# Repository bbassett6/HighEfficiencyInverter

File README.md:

Project Executive Summary

What is the design problem and why it should be solved?

With the growing popularity of student-led solar car racing competitions, newly established teams can have restrictive levels of funding to start their engineering endeavors. One of the most critical components of the competitiveness of their cars is the powertrain efficiency, which is heavily influenced by the quality and versatility of their motor controller. As of today, there are only two competitive options that are adopted by most teams, and both represent a substantial amount of the vehicle's cost (over a third of the electrical system's, approximately). This creates a tall barrier of entry for developing engineers to be exposed to real-life design environments that could deeply affect their career choices and subsequent impact in the world, which is why an open-source, accessible inverter would be impactful in the field of sustainable energy, and potentially many others.

What are the technical problems?

Technical problems include
•	Obtaining efficiency range values comparable or superior to present competitors’ while offering a substantially reduced price: 
Because of the size of the market, no substantial innovation has been made in mainstream options for approximately 14 years. Recent developments in SiC and GaN-based semiconductors could contribute a significant advantage compared to these outdated designs, but hitting required performance levels for a large range of possible motor and voltage configurations will be a challenge. Additionally, new control methodologies might be more applicable nowadays because of both device development and advances in control theory.
•	Maximizing efficiency while keeping the inverter design as tolerant as possible to high-voltage design changes depending on the application: 
Teams' choices of power per motor and DC bus voltage can vary drastically depending on the competition segment (multi- or single-occupant vehicles), creating a challenging optimization problem when attempting to make a product as efficient as possible for as many configurations as expected.
•	Minimizing inverter-driven high voltage system requirements: 
In addition to the DC bus compatibility, motor and motor sensing versatility is a factor that influences how seamless the product's integration can be, facilitating its adoption and potentially expanding its impact.
•	Power density (gravimetric, volumetric):
Being heavily influenced by the switching speed of the semiconductor devices being employed, recent product releases could be incredibly important to meet performance levels such as the DOE's 2025 Vehicle Technology goals.

What is the overall design/technical/objective(s)?

Design a financially (under US$ 1000) and technically accessible, high efficiency inverter for use in solar vehicle applications. The design should be easily replicable, testable, and employed by high-school level students. The final efficiency characteristics for applicable performance ranges (e.g. torque, speed, temperature), should be compatible with or surpass those of available options (WaveSculptor22, Mitsuba).

What is the proof of concept? What demonstrates that the solution works?

The proof of concept for the project could consist of a custom-made PCB for the selected power stage topology, containing components such as the switching devices, gate drivers, & high-voltage sensors. This would be complemented with an off-the-shelf development board containing the selected microcontroller and required peripherals, allowing full validation and operation of the converter without a finalized case and custom logic-stage PCB. Should this implementation work as expected, the project would move forward to unification and/or further customization of the boards to achieve a final unified package that is easily integrable.

Demonstrating the solution may involve attaching either an inductive load or a real motor to the inverter and measuring power losses through the power stage at various operating points (steady state cruising, acceleration, regenerative braking).

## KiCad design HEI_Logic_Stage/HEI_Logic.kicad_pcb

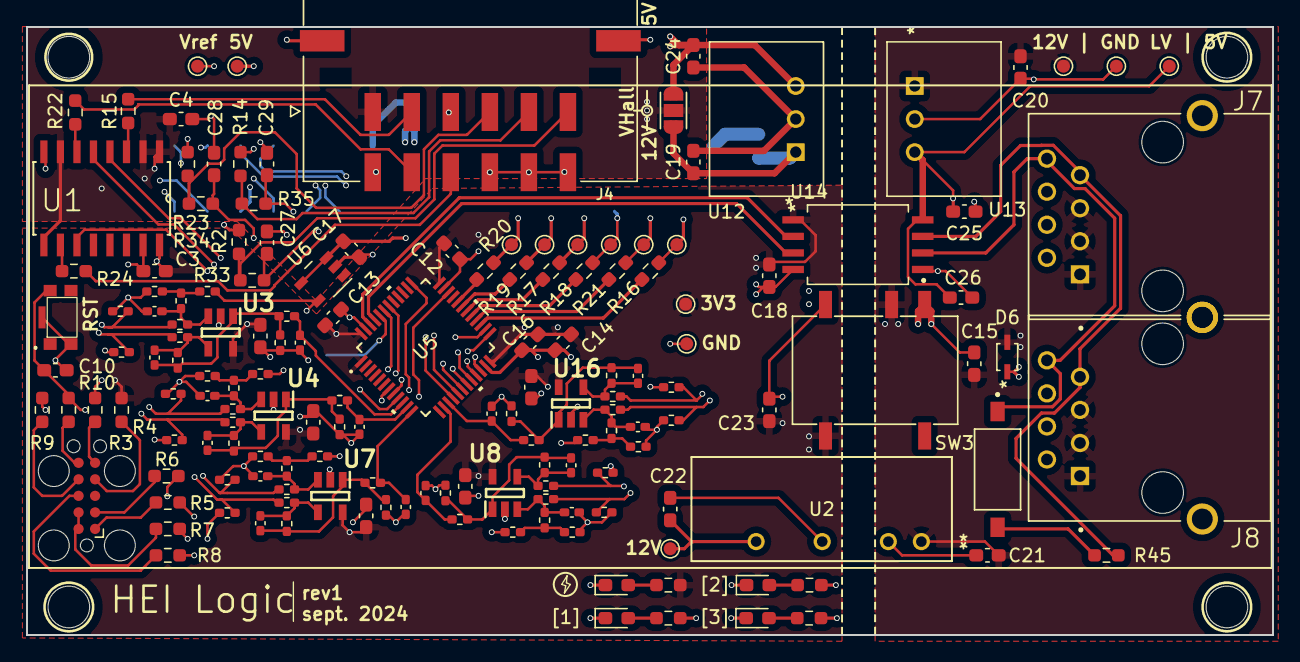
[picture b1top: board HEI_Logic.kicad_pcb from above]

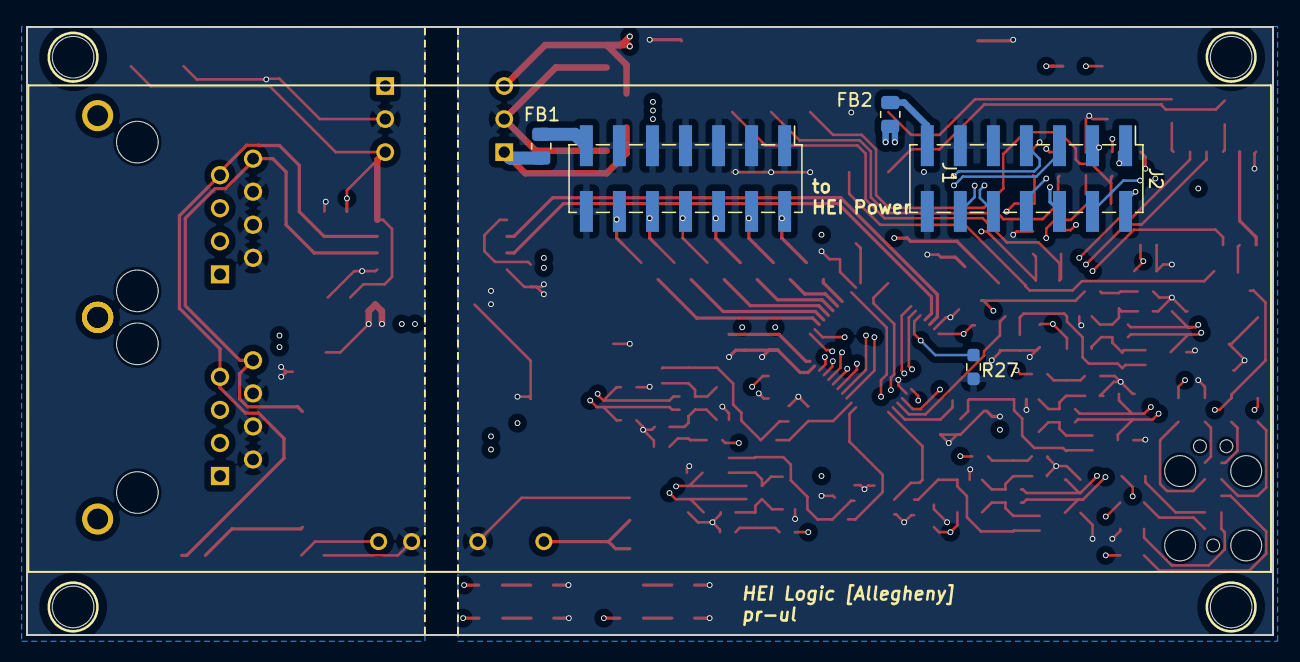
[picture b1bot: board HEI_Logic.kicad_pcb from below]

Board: 4 copper layers, 95.8 x 46.7 mm, 167 parts (5 on the bottom side), 99 nets.

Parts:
C1, C2, C3, C4, C10, C11, C12, C13, C14, C18, C26, C27, C28, C29, C39, C40: 0.1uF; C_0603_1608Metric_Pad1.08x0.95mm_HandSolder
C5, C9, C33, C38, C41: 33p; C_0402_1005Metric_Pad0.74x0.62mm_HandSolder
C6, C7, C8, C30, C31, C32, C34, C35, C36, C37: 0; C_0402_1005Metric_Pad0.74x0.62mm_HandSolder
C15: 2.2uF; C_0603_1608Metric_Pad1.08x0.95mm_HandSolder
C16: 4.7uF; C_0603_1608Metric_Pad1.08x0.95mm_HandSolder
C17: 4.7u; C_0603_1608Metric_Pad1.08x0.95mm_HandSolder
C19, C20, C23, C24, C25: 10uF; C_0603_1608Metric_Pad1.08x0.95mm_HandSolder
C21, C22: 1uF; C_0603_1608Metric_Pad1.08x0.95mm_HandSolder
D2: LED_Green; LED_0603_1608Metric_Pad1.05x0.95mm_HandSolder
D3, D4, D5: LED_Orange; LED_0603_1608Metric_Pad1.05x0.95mm_HandSolder
D6: 12V_TVS_ESD12VD3B-TP; ESD12VD3B-TP
FB1, FB2: R_0805_2012Metric
H1, H2, H3, H4: No. 8; MountingHole_2.1mm
J1, J2: Conn_02x07_Odd_Even; PinHeader_2x07_P2.54mm_Vertical_SMD
J3: Tag-Connect; Tag-Connect_TC2050-IDC-FP_2x05_P1.27mm_Vertical
J4: 430451210; MOLEX_430451210
J7: RJ_{1}; ASSMANN_A-2004-2-4-LPS-N-R
J8: RJ_{2}; ASSMANN_A-2004-2-4-LPS-N-R
JP2: Jumper_3_Open; SolderJumper-3_P1.3mm_Open_RoundedPad1.0x1.5mm_NumberLabels
R1: 100; R_0603_1608Metric_Pad0.98x0.95mm_HandSolder
R2, R14, R23: X; R_0603_1608Metric_Pad0.98x0.95mm_HandSolder
R3, R4, R5, R6, R7, R8, R9, R10: 150; R_0603_1608Metric_Pad0.98x0.95mm_HandSolder
R11, R12, R13: 220; R_0603_1608Metric_Pad0.98x0.95mm_HandSolder
R15, R16, R17, R18, R19, R20, R21, R22, R24, R33, R34, R35: 330; R_0603_1608Metric_Pad0.98x0.95mm_HandSolder
R25, R26, R28, R29, R30, R38, R39, R43, R44, R46, R49, R50, R52, R54, R56, R57, R59, R62, R65, R68, R70, R73, R75, R77, R78: 10k; R_0402_1005Metric_Pad0.72x0.64mm_HandSolder
R27: 10k; R_0603_1608Metric_Pad0.98x0.95mm_HandSolder
R31, R32, R36, R37, R55, R58, R63, R64, R66, R67, R72: 40k; R_0402_1005Metric_Pad0.72x0.64mm_HandSolder
R40, R47, R53, R60: 25k; R_0402_1005Metric_Pad0.72x0.64mm_HandSolder
R41, R48, R61, R69: 30k; R_0402_1005Metric_Pad0.72x0.64mm_HandSolder
R42, R51, R74, R76, R79: 120; R_0402_1005Metric_Pad0.72x0.64mm_HandSolder
R45: 120; R_0603_1608Metric_Pad0.98x0.95mm_HandSolder
R71: 35k; R_0402_1005Metric_Pad0.72x0.64mm_HandSolder
SW1: KMR223GLFG
SW3: SW_SPST; SW_DS04-254-1-01BK-SMT
TP1, TP2, TP11, TP15, TP16, TP17, TP18, TP19, TP20, TP21, TP24, TP25, TP26, TP27: Test_Point; TestPoint_Pad_D1.0mm
U1: CD40109BQNSRQ1; SOIC127P780X200-16N
U2: TMH 1212S; TMH SINGLE_TRP
U3, U4, U7, U8, U16: TLV9051IDBVR; SOT95P280X145-5N
U5: STM32F334C8T6; LQFP48-7x7mm
U6: LM4132BMF-3.3; 3V_Ref_LM4132AQ1MFT3.0_SOT235
U9: PDS1-S12-S3-M; CONV_PDS1-S12-S3-M
U12, U13: 5V_Converter_R-78E5.0-0.5; R-78E5.0-0.5
U14: ADM3058EBRIZ; 8-SOIC_ADM3058EBRIZ

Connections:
+3V3: C1.1, C2.1, C3.1, C11.1, C12.2, C13.2, C14.2, C16.1, C18.2, C23.1, C39.1, C40.1, R1.2, R4.1, TP15.1, U1.16 (VDD), U3.5 (V+), U4.5 (V+), U5.1 (VBAT), U5.24 (VDD_1), U5.36 (VDDUSB), U5.48 (VDD_2), U7.5 (V+), U8.5 (V+), U9.5 (+VO), U14.1 (VDD1), U16.5 (V+)
+5V: C17.1, C24.1, FB2.2, JP2.1 (A), TP18.1, U6.3 (EN), U6.4 (VIN), U12.3 (+VOUT)
+5V_CAN: C25.1, C26.2, TP19.1, U13.3 (+VOUT), U14.8 (VDD2)
+12V_LV: C15.1, C20.1, C21.1, D6.2, J7.1, J7.3, J7.5, J8.1, J8.3, J8.5, TP1.1, U2.1 (+VIN(VCC)), U9.2 (VIN), U13.1 (+VIN)
+12V_MCU: C19.1, C22.1, FB1.2, JP2.3 (B), TP17.1, U2.6 (+VOUT), U12.1 (+VIN)
/CAN_RX: U5.45 (PB8), U14.3 (RXD)
/CAN_TX: U5.46 (PB9), U14.2 (TXD)
/Control & Motor Interface/A+: C31.2, R37.2, R40.2, U3.3 (IN+)
/Control & Motor Interface/A-: C30.1, R36.2, R41.1, U3.4 (IN-)
/Control & Motor Interface/Ao: C30.2, R41.2, R42.1, R73.2, U3.1 (OUT)
/Control & Motor Interface/B+: C36.2, R53.2, R67.2, U4.3 (IN+)
/Control & Motor Interface/B-: C32.1, R66.2, R69.1, U4.4 (IN-)
/Control & Motor Interface/Bo: C32.2, R69.2, R70.2, R74.1, U4.1 (OUT)
/Control & Motor Interface/C+: C8.2, R32.2, R47.2, U7.3 (IN+)
/Control & Motor Interface/C-: C7.1, R31.2, R48.1, U7.4 (IN-)
/Control & Motor Interface/Co: C7.2, R48.2, R50.2, R51.1, U7.1 (OUT)
/Control & Motor Interface/D+: C37.2, R58.2, R60.2, U8.3 (IN+)
/Control & Motor Interface/D-: C35.1, R55.2, R61.1, U8.4 (IN-)
/Control & Motor Interface/DCIsense+: J2.7, R52.2, R58.1
/Control & Motor Interface/DCIsenseRef: J2.5, R54.2, R55.1
/Control & Motor Interface/DCVsense+: J2.3, R28.2, R64.1
/Control & Motor Interface/DCVsense-: J2.1, R62.2, R63.1
/Control & Motor Interface/Do: C35.2, R61.2, R75.2, R76.1, U8.1 (OUT)
/Control & Motor Interface/E+: C34.2, R64.2, R71.2, U16.3 (IN+)
/Control & Motor Interface/E-: C6.1, R63.2, R72.1, U16.4 (IN-)
/Control & Motor Interface/Eo: C6.2, R72.2, R78.2, R79.1, U16.1 (OUT)
/Control & Motor Interface/HallIN1: R15.1, U1.3 (A)
/Control & Motor Interface/HallIN2: R22.2, U1.6 (B)
/Control & Motor Interface/HallIN3: R24.2, U1.10 (C)
/Control & Motor Interface/PhA_Isense+: J2.2, R37.1, R38.2
/Control & Motor Interface/PhA_IsenseRef: J2.4, R36.1, R39.2
/Control & Motor Interface/PhB_Isense+: J2.6, R43.2, R67.1
/Control & Motor Interface/PhB_IsenseRef: J2.8, R44.2, R66.1
/Control & Motor Interface/PhC_Isense+: J2.10, R29.2, R32.1
/Control & Motor Interface/PhC_IsenseRef: J2.12, R30.2, R31.1
/Control & Motor Interface/TIN1_r: J4.4, R23.2, R34.1
/Control & Motor Interface/TIN2_r: J4.5, R14.2, R35.1
/Control & Motor Interface/TIN3_r: J4.6, R2.2, R33.1
/DCI: C38.1, R76.2, U5.14 (PA4)
/DCV: C41.1, R79.2, U5.15 (PA5)
/HRTIM_A1: J1.8, R18.1, TP25.1
/HRTIM_A1_r: R18.2, U5.29 (PA8)
/HRTIM_A2: J1.6, R17.1, TP24.1
/HRTIM_A2_r: R17.2, U5.30 (PA9)
/HRTIM_B1: J1.4, R19.1, TP21.1
/HRTIM_B1_r: R19.2, U5.31 (PA10)
/HRTIM_B2: J1.2, R20.1, TP20.1
/HRTIM_B2_r: R20.2, U5.32 (PA11)
/HRTIM_D1: J1.12, R16.2, TP27.1
/HRTIM_D1_r: R16.1, U5.27 (PB14)
/HRTIM_D2: J1.10, R21.2, TP26.1
/HRTIM_D2_r: R21.1, U5.28 (PB15)
/HallIN1_3v3: U1.4 (E), U5.18 (PB0)
/HallIN2_3v3: U1.5 (F), U5.19 (PB1)
/HallIN3_3v3: U1.11 (G), U5.21 (PB10)
/LED1: R13.2, U5.26 (PB13)
/LED2: R12.2, U5.25 (PB12)
/LED3: R11.2, U5.22 (PB11)
/PhA_I: C5.1, R42.2, U5.10 (PA0)
/PhB_I: C33.1, R74.2, U5.11 (PA1)
/PhC_I: C9.1, R51.2, U5.12 (PA2)
/Power & CAN/CANH: J7.7, J8.7, R45.1, U14.7 (CANH)
/Power & CAN/CANL: J7.8, J8.8, SW3.1 (A), U14.6 (CANL)
/SWDCLK: R9.1, U5.37 (PA14)
/SWDIO: R8.1, U5.34 (PA13)
/TIN1: C28.1, R34.2, U5.16 (PA6)
/TIN2: C29.1, R35.2, U5.17 (PA7)
/TIN3: C27.1, R33.2, U5.20 (PB2)
/UART_RX: R6.1, U5.43 (PB7)
/UART_TX: R5.2, U5.42 (PB6)
/Vref: R2.1, R14.1, R23.1, R25.2, R46.2, R56.2, R59.2, R65.2, TP11.1, U5.9 (VDDA/VREF_P), U6.5 (VREF)
/~RST: C10.1, R10.1, SW1.4, U5.7 (~RST)
GND: C1.2, C2.2, C3.2, C4.2, C5.2, C8.1, C9.2, C10.2, C11.2, C12.1, C13.1, C14.1, C16.2, C17.2, C18.1, C19.2, C22.2, C23.2, C24.2, C27.2, C28.2, C29.2, C31.1, C33.2, C34.1, C36.1, C37.1, C38.2, C39.2, C40.2, C41.2, D2.1 (K), D3.1 (K), D4.1 (K), D5.1 (K), J1.1, J1.3, J1.5, J1.7, J1.9, J1.11, J1.14, J2.9, J2.11, J2.14, J4.3, J4.7, J4.10, J4.11, J4.12, J4.S1 (SHIELD1), J4.S2 (SHIELD2), R3.1, R7.1, R26.1, R27.1, R28.1, R29.1, R30.1, R38.1, R39.1, R43.1, R44.1, R49.1, R50.1, R52.1, R54.1, R57.1, R62.1, R68.1, R70.1, R73.1, R75.1, R77.1, R78.1, SW1.2, SW1.G1, TP16.1, U1.8 (VSS), U1.15 (EN_D), U2.4 (-VOUT), U3.2 (V-), U4.2 (V-), U5.8 (VSSA/VREF_M), U5.23 (VSS_1), U5.35 (VSS_2), U5.47 (VSS_3), U6.2 (GND), U7.2 (V-), U8.2 (V-), U9.4 (0V), U12.2 (GND), U14.4 (GND1), U16.2 (V-)
GND_LV: C15.2, C20.2, C21.2, C25.2, C26.1, D6.1, J7.2, J7.4, J7.6, J8.2, J8.4, J8.6, TP2.1, U2.2 (-VIN(GND)), U9.1 (GND), U13.2 (GND), U14.5 (GND2)
unnamed: D2.2 (A), R1.1
unnamed: D3.2 (A), R11.1
unnamed: D4.2 (A), R12.1
unnamed: D5.2 (A), R13.1
unnamed: FB1.1, J1.13
unnamed: FB2.1, J2.13
unnamed: J3.1, R5.1
unnamed: J3.2, R6.2
unnamed: J3.4, R4.2
unnamed: J3.5, R3.2
unnamed: J3.6, R10.2
unnamed: J3.7, R9.2
unnamed: J3.8, R8.2
unnamed: J3.9, J3.10, R7.2
unnamed: J4.2, R15.2
unnamed: J4.8, R22.1
unnamed: J4.9, R24.1
unnamed: R25.1, R26.2, R53.1
unnamed: R40.1, R56.1, R57.2
unnamed: R46.1, R47.1, R49.2
unnamed: R59.1, R60.1, R68.2
unnamed: R65.1, R71.1, R77.2
unnamed: R45.2, SW3.2 (B)
unnamed: R27.2, U5.44 (PH3-BOOT0)
V_Hall: C4.1, J4.1, JP2.2 (C), U1.1 (VCC), U1.2 (EN_A), U1.7 (EN_B), U1.9 (EN_C)

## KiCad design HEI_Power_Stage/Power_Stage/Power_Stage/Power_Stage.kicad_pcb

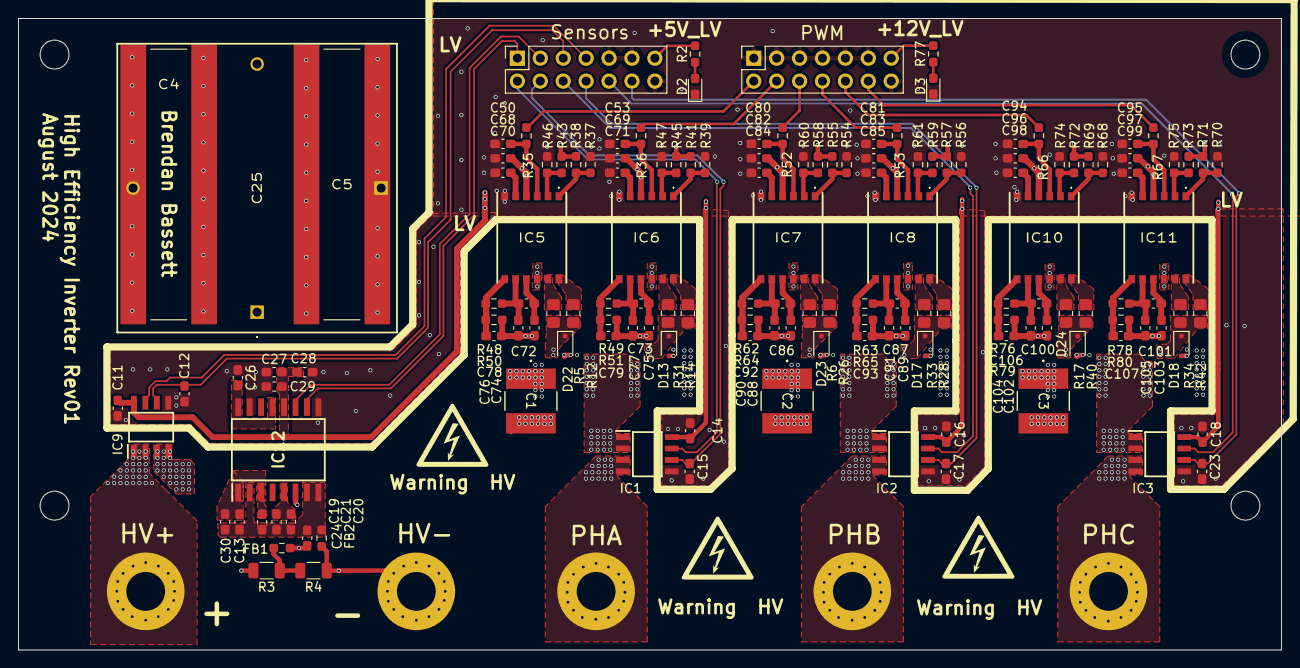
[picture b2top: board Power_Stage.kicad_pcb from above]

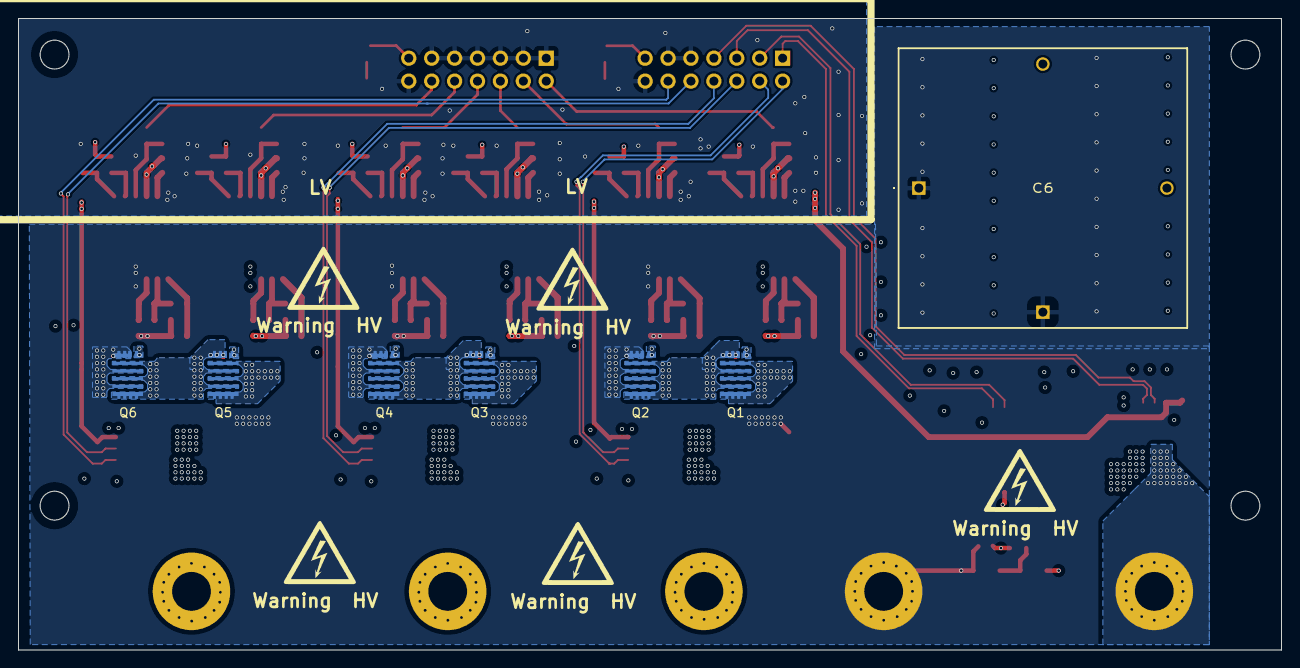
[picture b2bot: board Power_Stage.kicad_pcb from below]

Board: 6 copper layers, 140.0 x 70.0 mm, 163 parts (7 on the bottom side), 96 nets.

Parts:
C1, C2, C3: 3.3uF; CAP_6050_TDK
C4, C5: B58035U5106M001
C6, C25: 15uF; C4AQLLU5150A19K
C11, C14, C16, C18, C19, C20, C26, C72, C73, C74, C75, C76, C77, C86, C87, C88, C89, C90, C91, C100, C101, C102, C103, C104, C105: 100nF; C_0603_1608Metric_Pad1.08x0.95mm_HandSolder
C12, C13, C15, C17, C21, C23, C29: 1nF; C_0603_1608Metric_Pad1.08x0.95mm_HandSolder
C24, C50, C53, C78, C79, C80, C81, C92, C93, C94, C95, C106, C107: 100pF; C_0603_1608Metric_Pad1.08x0.95mm_HandSolder
C27, C30, C68, C69, C70, C71, C82, C83, C84, C85, C96, C97, C98, C99: 1uF; C_0603_1608Metric_Pad1.08x0.95mm_HandSolder
C28: 2.2uF; C_0603_1608Metric_Pad1.08x0.95mm_HandSolder
D2, D3: G; LED_0603_1608Metric_Pad1.05x0.95mm_HandSolder
D13, D17, D18, D22, D23, D24: PDZVTFTR5.1B; D_SOD-323F
FB1, FB2: R_0603_1608Metric_Pad0.98x0.95mm_HandSolder
H1, H2, H3, H4: No. 8; MountingHole_3.2mm_M3
IC1, IC2, IC3, IC9: ACS730KLCTR-65ABT; SOIC127P600X175-8N
IC5, IC6, IC7, IC8, IC10, IC11: AHV85111KNHTR
IC12: AMC3311QDWERQ1; SOIC127P1030X265-16N
J1, J2, J3, J4, J5: Screw_Terminal_01x01; MountingHole_4.3mm_M4_Pad
J8, J9: Conn_02x07_Odd_Even; PinSocket_2x07_P2.54mm_Vertical
Q1, Q2, Q3, Q4, Q5, Q6: EPC2304ENGRT; EPC2304_ECC
R2: 440; R_0603_1608Metric_Pad0.98x0.95mm_HandSolder
R3: 1Meg; R_1206_3216Metric
R4: 10k; R_1206_3216Metric
R5, R6, R17, R31, R33, R34: 0; R_0805_2012Metric_Pad1.20x1.40mm_HandSolder
R12, R14, R26, R28, R40, R42: 0.47; R_0805_2012Metric_Pad1.20x1.40mm_HandSolder
R35, R36, R37, R38, R39, R41, R46, R47, R52, R53, R54, R55, R56, R57, R60, R61, R66, R67, R68, R69, R70, R71, R74, R75: 0; R_0603_1608Metric_Pad0.98x0.95mm_HandSolder
R43, R45, R50, R51, R58, R59, R64, R65, R72, R73, R79, R80: 100k; R_0603_1608Metric_Pad0.98x0.95mm_HandSolder
R48, R49, R62, R63, R76, R78: 32.4k; R_0603_1608Metric_Pad0.98x0.95mm_HandSolder
R77: 1.2k; R_0603_1608Metric_Pad0.98x0.95mm_HandSolder

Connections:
+5V_LV: C11.1, C14.1, C16.1, C18.1, C27.2, C28.2, C29.1, IC1.8 (VCC), IC2.8 (VCC), IC3.8 (VCC), IC9.8 (VCC), IC12.12 (VDD), J9.13, R2.2
+12V_LV: C68.1, C69.1, C82.1, C83.1, C96.1, C97.1, IC5.4 (VDRV), IC6.4 (VDRV), IC7.4 (VDRV), IC8.4 (VDRV), IC10.4 (VDRV), IC11.4 (VDRV), J8.13, R38.1, R41.1, R43.1, R45.1, R55.1, R57.1, R58.1, R59.1, R69.1, R71.1, R72.1, R73.1, R77.2
/AHS_{PWM}: J8.2, R35.1
/ALS_{PWM}: J8.4, R36.1
/BHS_{PWM}: J8.6, R52.1
/BLS_{PWM}: J8.8, R53.1
/CHS_{PWM}: J8.10, R66.1
/CLS_{PWM}: J8.12, R67.1
/DCI_{sense}+: IC9.7 (VIOUT), J9.7
/DCI_{sense}-: C12.1, IC9.6 (VZCR), J9.5
/DCV_{sense}+: IC12.11 (OUTP), J9.3
/DCV_{sense}-: IC12.10 (OUTN), J9.1
/PHA: IC1.3 (IP-_1), IC1.4 (IP-_2), J2.1
/PHAI_{sense}+: IC1.7 (VIOUT), J9.2
/PHAI_{sense}-: C15.1, IC1.6 (VZCR), J9.4
/PHB: IC2.3 (IP-_1), IC2.4 (IP-_2), J1.1
/PHBI_{sense}+: IC2.7 (VIOUT), J9.6
/PHBI_{sense}-: C17.1, IC2.6 (VZCR), J9.8
/PHC: IC3.3 (IP-_1), IC3.4 (IP-_2), J3.1
/PHCI_{sense}+: IC3.7 (VIOUT), J9.10
/PHCI_{sense}-: C23.1, IC3.6 (VZCR), J9.12
/Phase1/HS_{Gate}: D22.1 (K), Q1.1, R5.2, R12.2
/Phase1/HS_{SNK}: IC5.11 (OUTPD), R5.1
/Phase1/HS_{SRC}: IC5.12 (OUTPU), R12.1
/Phase1/LS_{Gate}: D13.1 (K), Q2.1, R14.2, R31.2
/Phase1/LS_{SNK}: IC6.11 (OUTPD), R31.1
/Phase1/LS_{SRC}: IC6.12 (OUTPU), R14.1
/Phase1/SW: C74.2, C76.2, C78.2, D22.2 (A), IC1.1 (IP+_1), IC1.2 (IP+_2), IC5.10 (SOURCE), Q1.2, Q1.4, Q1.6, Q2.3, Q2.5, Q2.7, R50.1
/Phase1/en: IC6.2 (EN), R45.2, R47.1
/Phase1/hen: IC5.2 (EN), R43.2, R46.1
/Phase1/hfb: C78.1, IC5.7 (FB), R48.1, R50.2
/Phase1/hpwm: C50.1, IC5.3 (IN), R35.2
/Phase1/hsel: IC5.1 (SEL), R37.2, R38.2
/Phase1/hvsecn: C72.2, C74.1, IC5.9 (VSECN)
/Phase1/hvsecp: C72.1, C76.1, IC5.8 (VSECP), R48.2
/Phase1/lfb: C79.1, IC6.7 (FB), R49.1, R51.2
/Phase1/lpwm: C53.1, IC6.3 (IN), R36.2
/Phase1/lsel: IC6.1 (SEL), R39.2, R41.2
/Phase1/lvsecn: C73.2, C75.1, IC6.9 (VSECN)
/Phase1/lvsecp: C73.1, C77.1, IC6.8 (VSECP), R49.2
/Phase2/HS_{Gate}: D23.1 (K), Q3.1, R6.2, R26.2
/Phase2/HS_{SNK}: IC7.11 (OUTPD), R6.1
/Phase2/HS_{SRC}: IC7.12 (OUTPU), R26.1
/Phase2/LS_{Gate}: D17.1 (K), Q4.1, R28.2, R33.2
/Phase2/LS_{SNK}: IC8.11 (OUTPD), R33.1
/Phase2/LS_{SRC}: IC8.12 (OUTPU), R28.1
/Phase2/SW: C88.2, C90.2, C92.2, D23.2 (A), IC2.1 (IP+_1), IC2.2 (IP+_2), IC7.10 (SOURCE), Q3.2, Q3.4, Q3.6, Q4.3, Q4.5, Q4.7, R64.1
/Phase2/en: IC8.2 (EN), R59.2, R61.1
/Phase2/hen: IC7.2 (EN), R58.2, R60.1
/Phase2/hfb: C92.1, IC7.7 (FB), R62.1, R64.2
/Phase2/hpwm: C80.1, IC7.3 (IN), R52.2
/Phase2/hsel: IC7.1 (SEL), R54.2, R55.2
/Phase2/hvsecn: C86.2, C88.1, IC7.9 (VSECN)
/Phase2/hvsecp: C86.1, C90.1, IC7.8 (VSECP), R62.2
/Phase2/lfb: C93.1, IC8.7 (FB), R63.1, R65.2
/Phase2/lpwm: C81.1, IC8.3 (IN), R53.2
/Phase2/lsel: IC8.1 (SEL), R56.2, R57.2
/Phase2/lvsecn: C87.2, C89.1, IC8.9 (VSECN)
/Phase2/lvsecp: C87.1, C91.1, IC8.8 (VSECP), R63.2
/Phase3/HS_{Gate}: D24.1 (K), Q5.1, R17.2, R40.2
/Phase3/HS_{SNK}: IC10.11 (OUTPD), R17.1
/Phase3/HS_{SRC}: IC10.12 (OUTPU), R40.1
/Phase3/LS_{Gate}: D18.1 (K), Q6.1, R34.2, R42.2
/Phase3/LS_{SNK}: IC11.11 (OUTPD), R34.1
/Phase3/LS_{SRC}: IC11.12 (OUTPU), R42.1
/Phase3/SW: C102.2, C104.2, C106.2, D24.2 (A), IC3.1 (IP+_1), IC3.2 (IP+_2), IC10.10 (SOURCE), Q5.2, Q5.4, Q5.6, Q6.3, Q6.5, Q6.7, R79.1
/Phase3/en: IC11.2 (EN), R73.2, R75.1
/Phase3/hen: IC10.2 (EN), R72.2, R74.1
/Phase3/hfb: C106.1, IC10.7 (FB), R76.1, R79.2
/Phase3/hpwm: C94.1, IC10.3 (IN), R66.2
/Phase3/hsel: IC10.1 (SEL), R68.2, R69.2
/Phase3/hvsecn: C100.2, C102.1, IC10.9 (VSECN)
/Phase3/hvsecp: C100.1, C104.1, IC10.8 (VSECP), R76.2
/Phase3/lfb: C107.1, IC11.7 (FB), R78.1, R80.2
/Phase3/lpwm: C95.1, IC11.3 (IN), R67.2
/Phase3/lsel: IC11.1 (SEL), R70.2, R71.2
/Phase3/lvsecn: C101.2, C103.1, IC11.9 (VSECN)
/Phase3/lvsecp: C101.1, C105.1, IC11.8 (VSECP), R78.2
/dcdc_out: C13.1, C19.1, C30.1, IC12.1 (DCDC_OUT), IC12.3 (HLDO_IN)
/hgnd: C13.2, C19.2, C20.2, C21.2, C24.2, C30.2, FB2.2, IC12.2 (DCDC_HGND), IC12.7 (HGND_1), IC12.8 (HGND_2)
/hldo_out: C20.1, C21.1, IC12.5 (HLDO_OUT)
/vsnsin: C24.1, FB1.2, IC12.6 (IN)
GND: C11.2, C12.2, C14.2, C15.2, C16.2, C17.2, C18.2, C23.2, C26.1, C27.1, C28.1, C29.2, C50.2, C53.2, C68.2, C69.2, C70.1, C71.1, C80.2, C81.2, C82.2, C83.2, C84.1, C85.1, C94.2, C95.2, C96.2, C97.2, C98.1, C99.1, D2.1 (K), D3.1 (K), IC1.5 (GND), IC2.5 (GND), IC3.5 (GND), IC5.6 (GND), IC6.6 (GND), IC7.6 (GND), IC8.6 (GND), IC9.5 (GND), IC10.6 (GND), IC11.6 (GND), IC12.9 (GND), IC12.15 (DCDC_GND), J8.1, J8.3, J8.5, J8.7, J8.9, J8.11, J8.14, J9.9, J9.11, J9.14, R37.1, R39.1, R46.2, R47.2, R54.1, R56.1, R60.2, R61.2, R68.1, R70.1, R74.2, R75.2
HV+: C1.1, C2.1, C3.1, C4.2, C5.2, C6.2, C25.2, IC9.3 (IP-_1), IC9.4 (IP-_2), Q1.3, Q1.5, Q1.7, Q3.3, Q3.5, Q3.7, Q5.3, Q5.5, Q5.7, R3.2
HV+in: IC9.1 (IP+_1), IC9.2 (IP+_2), J4.1
HV-: C1.2, C2.2, C3.2, C4.1, C5.1, C6.1, C25.1, C75.2, C77.2, C79.2, C89.2, C91.2, C93.2, C103.2, C105.2, C107.2, D13.2 (A), D17.2 (A), D18.2 (A), FB2.1, IC6.10 (SOURCE), IC8.10 (SOURCE), IC11.10 (SOURCE), J5.1, Q2.2, Q2.4, Q2.6, Q4.2, Q4.4, Q4.6, Q6.2, Q6.4, Q6.6, R4.1, R51.1, R65.1, R80.1
unnamed: D2.2 (A), R2.1
unnamed: D3.2 (A), R77.1
unnamed: FB1.1, R3.1, R4.2
unnamed: C70.2, IC5.5 (REF)
unnamed: C71.2, IC6.5 (REF)
unnamed: C84.2, IC7.5 (REF)
unnamed: C85.2, IC8.5 (REF)
unnamed: C98.2, IC10.5 (REF)
unnamed: C99.2, IC11.5 (REF)
unnamed: C26.2, IC12.13 (LDO_OUT), IC12.16 (DCDC_IN)

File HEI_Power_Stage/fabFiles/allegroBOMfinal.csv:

Reference,Value,Qty,DKPN,Mouser PN,Manufacturer,MPN,Datasheet,Footprint
"C1,C2,C3",3.3uF,3,445-7108-1-ND,,tdk,CKG57NX7T2E335M500JH,https://www.digikey.com/en/products/detail/tdk-corporation/C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,GTSR:CAP_6050_TDK
"C4,C5",B58035U5106M001,2,495-B58035U5106M001-ND,,epcos tdk,B58035U5106M001,https://product.tdk.com/system/files/dam/doc/product/capacit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,B58035U5106M001_KiCad:B58035U5106M001
"C6,C25",15uF,2,399-C4AQLLU5150A19K-ND,,kemet,C4AQLLU5150A19K,https://www.kemet.com/specsheet/C4AQLLU5150A19K,C4AQLLU5150A19K _KiCad:C4AQLLU5150A19K
"C11,C14,C16,C18,C19,C20,C26,C72,C73,C74,C75,C76,C77,C86,C87,C88,C89,C90,C91,C100,C101,C102,C103,C104,C105",100nF,25,1276-1000-1-ND,,samsung,CL10B104KB8NNNC,-- mixed values --,Capacitor_SMD:C_0603_1608Metric_Pad1.08x0.95mm_HandSolder
"C12,C13,C15,C17,C21,C23,C29",1nF,7,490-4777-1-ND,,murata,GCM188R71H102KA37D,-- mixed values --,Capacitor_SMD:C_0603_1608Metric_Pad1.08x0.95mm_HandSolder
"C24,C50,C53,C78,C79,C80,C81,C92,C93,C94,C95,C106,C107",100pF,13,1276-1908-1-NDÊ,,samsung,CL10B101KB8NFNC,~,Capacitor_SMD:C_0603_1608Metric_Pad1.08x0.95mm_HandSolder
"C27,C30,C68,C69,C70,C71,C82,C83,C84,C85,C96,C97,C98,C99",1uF,14,490-10673-1-ND,,murata,GCM188R71E105KA64D,~,Capacitor_SMD:C_0603_1608Metric_Pad1.08x0.95mm_HandSolder
C28,2.2uF,1,490-4931-1-ND,,murata,GCM188R71H222KA37D,~,Capacitor_SMD:C_0603_1608Metric_Pad1.08x0.95mm_HandSolder
"D1,D2,D3",G,3,732-4971-1-ND,,wurth,150060GS75000,https://www.digikey.com/en/products/detail/liteon/LTST-C193T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,LED_SMD:LED_0603_1608Metric_Pad1.05x0.95mm_HandSolder
"D13,D17,D18,D22,D23,D24",PDZVTFTR5.1B,6,DDZ5V6ASF-7DICT-ND,,diodes inc,DDZ5V6ASF-7,https://www.rohm.com/datasheet?p=PDZVTF5.1B&dist=Digi-key&me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,Diode_SMD:D_SOD-323F
"FB1,FB2",~,2,490-1026-1-ND,,Murata,BLM18BD182SN1D,~,Resistor_SMD:R_0603_1608Metric_Pad0.98x0.95mm_HandSolder
"IC1,IC2,IC3,IC9",ACS730KLCTR-65ABT,4,,250-ACS730KLCTR65ABT,allegro,ACS730KLCTR-65AB-T,https://www.allegromicro.com/-/media/files/datasheets/acs730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,ACS730KLCTR65ABT_KiCad:SOIC127P600X175-8N
"IC5,IC6,IC7,IC8,IC10,IC11",AHV85111KNHTR,6,620-AHV85111KNHTRCT-NDÊ,,allegro,AHV85111KNHTR,https://www.allegromicro.com/~/media/files/datasheets/AHV851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,AHV85111_KiCad:AHV85111KNHTR
IC12,AMC3311QDWERQ1,1,,595-AMC3311QDWERQ1,TI,AMC3311QDWERQ1,https://www.ti.com/lit/ds/symlink/amc3311-q1.pdf?ts=17020178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,AMC3311_KiCad:SOIC127P1030X265-16N
"J8,J9",Conn_02x07_Odd_Even,2,S7110-ND,,sullins,PPPC072LFBN-RC,~,Connector_PinSocket_2.54mm:PinSocket_2x07_P2.54mm_Vertical
"Q1,Q2,Q3,Q4,Q5,Q6",EPC2304ENGRT,6,917-EPC2304ENGRTCT-ND,,epc,EPC2304ENGRT,https://www.digikey.com/en/products/detail/epc/EPC2304ENGRT/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,GTSR:EPC2304_ECC
"R1,R2",440,2,311-470GRCT-ND,,yageo,RC0603JR-07470RL,https://www.digikey.com/en/products/detail/panasonic-electro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,Resistor_SMD:R_0603_1608Metric_Pad0.98x0.95mm_HandSolder
R3,1Meg,1,YAG2022CT-ND,,yageo,RT1206BRD071ML,https://www.digikey.com/en/products/detail/yageo/RT1206BRD07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,Resistor_SMD:R_1206_3216Metric
R4,10k,1,YAG2329CT-ND,,yageo,RT1206BRD0710KL,https://www.digikey.com/en/products/detail/stackpole-electro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,Resistor_SMD:R_1206_3216Metric
"R5,R6,R17,R31,R33,R34",0 (0805),6,311-0.0ARCT-ND,,yageo,RC0805JR-070RL,,
"R35,R36,R38,R41,R52,R53,R55,R57,R66,R67,R69,R71,R37,R39,R46,R47,R54,R56,R60,R61,R68,R70,R74,R75",0,24,311-0.0GRCT-ND,,yageo,RC0603JR-070RL,~,-- mixed values --
"R12,R14,R26,R28,R40,R42",0.47,6,P.047AQCT-ND,,panansonic ec,ERJ-6BWFR047V,https://www.digikey.com/en/products/detail/panasonic-electro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,Resistor_SMD:R_0805_2012Metric_Pad1.20x1.40mm_HandSolder
"R43,R45,R50,R51,R58,R59,R64,R65,R72,R73,R79,R80",100k,12,311-100KHRCT-ND,,yageo,RC0603FR-07100KL,~,Resistor_SMD:R_0603_1608Metric_Pad0.98x0.95mm_HandSolder
"R48,R49,R62,R63,R76,R78",32.4k,6,311-32.4KHRCT-ND,,yageo,RC0603FR-0732K4L,~,Resistor_SMD:R_0603_1608Metric_Pad0.98x0.95mm_HandSolder
R77,1.2k,1,311-1.20KHRCT-ND,,yageo,RC0603FR-071K2L,https://www.digikey.com/en/products/detail/panasonic-electro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,Resistor_SMD:R_0603_1608Metric_Pad0.98x0.95mm_HandSolder

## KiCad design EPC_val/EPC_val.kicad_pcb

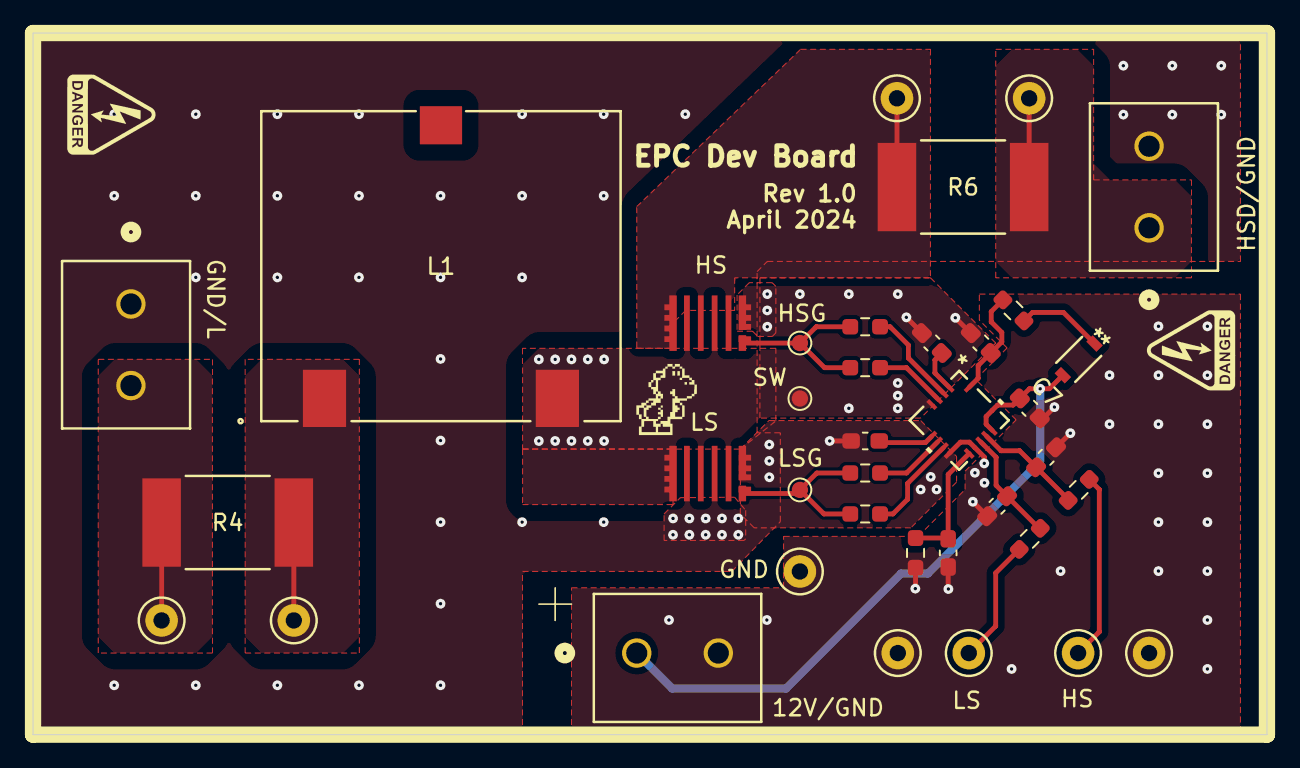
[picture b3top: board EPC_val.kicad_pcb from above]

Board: 4 copper layers, 75.6 x 43.0 mm, 37 parts (0 on the bottom side), 22 nets.

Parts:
12V/GND: 691137710002; CONN2_710002_WRE
C1, C2: 15pF; C_0603_1608Metric_Pad1.08x0.95mm_HandSolder
C3: 0.1uF; C_0603_1608Metric_Pad1.08x0.95mm_HandSolder
C4, C5, C7: 1uF; C_0603_1608Metric_Pad1.08x0.95mm_HandSolder
C6: 470nF; C_0603_1608Metric_Pad1.08x0.95mm_HandSolder
D1: RFU02VSM6STR; DIO_RFU02VS_ROM-M
GND: Test_Point; TestPoint_Keystone_5000-5004_Miniature
GND#2, GND#3: Test_Point; TestPoint_Keystone_5000-5004_Miniature
GND/L: 691137710002; CONN2_710002_WRE
HS: EPC2304ENGRT; EPC2304_ECC
HS#2: Test_Point; TestPoint_Keystone_5000-5004_Miniature
HSD/GND: 691137710002; CONN2_710002_WRE
HSG: Test_Point; TestPoint_Pad_D1.0mm
L1: 58 uH; IND_6000A_MUR
LS: EPC2304ENGRT; EPC2304_ECC
LS#2: Test_Point; TestPoint_Keystone_5000-5004_Miniature
LSG: Test_Point; TestPoint_Pad_D1.0mm
R1, R2: 2.2 0.1W; R_0603_1608Metric_Pad0.98x0.95mm_HandSolder
R3: 50k; R_0603_1608Metric_Pad0.98x0.95mm_HandSolder
R4, R6: PU3921FKM130U5L; RES_PU3921_.5mOHM_YAG-L
R5: 2 1/16W; R_0603_1608Metric_Pad0.98x0.95mm_HandSolder
R7, R9: 0.47 1/16W; R_0603_1608Metric_Pad0.98x0.95mm_HandSolder
R8, R10: 0 1/16W; R_0603_1608Metric_Pad0.98x0.95mm_HandSolder
SW: Test_Point; TestPoint_Pad_D1.0mm
TP5, TP6, TP7, TP8: Test_Point; TestPoint_Keystone_5000-5004_Miniature
U1: NCP51820AMNTWG; QFN_0AMNTWG_ONS-L

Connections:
+12V: 12V/GND.1, C7.1, D1.2 (A), U1.13 (EN), U1.14 (VDD)
/DT: C3.2, R3.2, U1.9 (DT)
/HIN: C1.1, R1.1, U1.12 (HIN)
/HSD: HS.3, HS.5, HS.7, R6.1, TP7.1
/HS_{Gate}: HS.1, HSG.1, R7.2, R8.2
/HS_{PWM}: HS#2.1, R1.2
/HS_{SNK}: R8.1, U1.3 (HOSNK)
/HS_{SRC}: R7.1, U1.2 (HOSRC)
/In_HSD: HSD/GND.1, R6.2, TP8.1
/In_L: GND/L.2, R4.1, TP5.1
/L: L1.1, R4.2, TP6.1
/LIN: C2.1, R2.1, U1.11 (LIN)
/LS_{Gate}: LS.1, LSG.1, R9.2, R10.2
/LS_{PWM}: LS#2.1, R2.2
/LS_{SNK}: R10.1, U1.7 (LSONK)
/LS_{SRC}: R9.1, U1.6 (LOSRC)
/SW: C4.2, C6.2, HS.2, HS.4, HS.6, L1.2, LS.3, LS.5, LS.7, SW.1, U1.4 (SW)
/VDDH: C4.1, U1.1 (VDDH)
/VDDL: C5.2, U1.5 (VDDL)
/V_{BST}: C6.1, R5.2, U1.15 (VBST)
GND: 12V/GND.2, C1.2, C2.2, C3.1, C5.1, C7.2, GND.1, GND#2.1, GND#3.1, GND/L.1, HSD/GND.2, LS.2, LS.4, LS.6, R3.1, U1.8 (PGND), U1.10 (SGND)
unnamed: D1.1 (K), R5.1

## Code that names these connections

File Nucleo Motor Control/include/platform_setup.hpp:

#ifndef __PLATFORM_SETUP
#define __PLATFORM_SETUP

#include "common.hpp"

void SystemClock_Config(void);
void GPIO_Init(void);
void Error_Handler(void);

#if PLATFORM_P_NUCLEO_IHM03
#define LED_PIN                                GPIO_PIN_5
#define LED_GPIO_PORT                          GPIOA
#define LED_GPIO_CLK_ENABLE()                  __HAL_RCC_GPIOA_CLK_ENABLE()
#endif

#if PLATFORM_HEI
// TODO: change these pin defs to the correct values
#define LED1_PIN                               GPIO_PIN_13
#define LED1_GPIO_PORT                         GPIOB
#define LED1_GPIO_CLK_ENABLE()                 __HAL_RCC_GPIOB_CLK_ENABLE()
#define LED2_PIN                               GPIO_PIN_11
#define LED2_GPIO_PORT                         GPIOB
#define LED2_GPIO_CLK_ENABLE()                 __HAL_RCC_GPIOB_CLK_ENABLE()
#define LED3_PIN                               GPIO_PIN_11
#define LED3_GPIO_PORT                         GPIOB
#define LED3_GPIO_CLK_ENABLE()                 __HAL_RCC_GPIOB_CLK_ENABLE()
#endif

#endif // __PLATFORM_SETUP

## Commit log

2024-02-23 testing
    testing
2024-02-23 basic GaN inverter LTSpice schematic
2024-03-01 updated git ignore for altium
    added altium file types to git ignore
2024-03-08 add files
2024-03-14 Basic schematic outline
    schematic files to start
2024-03-14 added epc gan fets library file
    stil trying to figure out how to have fully integrated database libraries because it will likely have a mix of custom and downloaded components
2024-03-15 gate driver model
    gate driver added
2024-03-15 added current sense IC library
    TMCS1123
    pin compatible with tmcs1133, higher bandwidth but not in production, can try to ask ti for samples if 250 kHz is not enough
2024-03-15 saved all documents
2024-03-15 removed all altium files from HEI repo
    removed all altium files to use repo as the Kicad repo
2024-03-15 kicad project
2024-03-16 added TMCS1123A1A
    added library for the tmcs1123 current sense
2024-03-16 updated tmcs1123 symbol
2024-03-16 added libraries
2024-03-17 kicad libs
2024-03-18 second try for kicad libs
2024-03-24 preliminary schematic and layout for POC
2024-03-25 initial phase a routing
    routed connections for phase A not including SPI. spi left as stubs that can be routed to connector and to the other ADCs.
    Power and PWRGND routing is done on layer 1,2,4 and can be discussed further in persons. For now I have VDC on layer 1 and 4. PWRGND on layer 1 and 4. SW and PHA on layer 1 and 2. layer 3 and 5 are g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
2024-03-27 SPI and ldo
    wired spi and ldo, thinking about stackup layer assignments for power. Layer 4 could be all VDC and PWD GND only, routing VDC on the top half and PWRGND on the bottom half. Then layer 1,2 can be for 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
2024-03-27 changes in meeting
2024-03-27 added 12-12 footprint
2024-03-29 layout
    5v regulators for each phase daq
    12v iso
    top half and bottom half planes
    SPi goes from bottom to top layer at plane split
    power routed on bottom two layers with solid planes
    switch nodes on top two layers
2024-03-29 latest changes
2024-03-31 changes since class on friday
    solid gndpwr plane on layer 3
    new cap... its large
2024-04-01 POC layout changes fro meeting
    Two cap options on the bottom:
    large kemet that would meet all requirements on its own
    also large cylindrical aluminum electrolytic that only has 4.3A riplpe current rating. can use either for testing. can also add more holes for trying other caps
    layer 3 now continous gndpwr for whole board.
2024-04-01 silkscreen updates
    silkscreen should be all good
    drc silkscreen errors somewhat resolved
    added labels for TPs and LEDs
    added more stitching for top layer "gnd" on top half tor PWM ref
    holes all alligned
2024-04-03 small changes
2024-04-03 low profile cap footprint and gitignore updates
2024-04-05 added low pass filters, PGND/SGND jumper
2024-04-10 spi isolation
2024-04-10 more isolation
2024-04-12 EPC test board
2024-04-12 need to fix vias
2024-04-12 git ignore pls work
2024-04-12 ignore .zip
2024-04-19 epc board should be ready to order
2024-04-19 added updated logic stage
2024-04-19 silkscreen,
2024-04-19 logic stage motor interface schematic
2024-04-21 layouted updated HEI-Logic
2024-08-21 added option for dc link
    https://www.digikey.com/en/products/detail/epcos-tdk-electronics/B58035U5106M001/7100511
2024-08-21 new gate driver
    added new gate drivers, changes sensing to be non isolated, removed adcs on gate drive pages, added connector, added dc link cap, need to still change isolation page to just be iso amp, need to adjus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
2024-08-21 new power stage schematic
    added iso amp for hv bus sensing
    updated connectors
    removed isolation page
    added notes for new components
    need to decide if ADCs go on power or logic board for noise immunity or simpler power stage
2024-08-22 added second option for isolated amplifier
    added adum4195 and idolated dcdc
    new iso amp is single ended output so we can use regular single ended input ADC
2024-08-22 hv label
2024-08-23 initial edits to logic stage schematic
2024-08-23 added new current sense
2024-08-25 I think all schematic done
    added new mps gate driver, new acs current sense, new differential voltage sense, new 5-5 iso converters.
    beginning layout
2024-08-25 more progress
    started placement for each half bridge
    3d bodies
    connectors sorted
    options for dc link cap
2024-08-26 placement rough draft
    roughly placed all components
2024-08-26 some change
2024-08-26 major logic stage updates
2024-08-26 new parts into Parts
2024-08-26 more minor updates
2024-08-27 all initial placement
    initial placement done
    routing for one stage done and copied
    will make edits and recopy later but wanted to see preview
    12.2 x 7.4cm
2024-08-27 add working "trapezoidal" sim
2024-08-27 big layout change
2024-08-28 almost complete routing
2024-08-28 board done
    drc just has silk overlaps and mosfet footprint related spacing issues because I was conservative with spacing.
2024-08-28 stuff
2024-08-29 allegro gate driver version schematic overhall and layout
    layout and routing almost complete for allegro gate drivers
2024-08-29 allegro power stage routed
    needs drc check and silkscreen for all components
2024-08-29 done
    silkscreen done and bom done in digikey
2024-08-31 some changes
    isolated amplifier now self powered so removed old amp and iso power supply
    gate return paths now on layer two
2024-09-02 changed dimensions and hole spacing
    70x140mm
    holes 4mm from edges on top left and right, 16mm from bottom
2024-09-03 logic stage diff amp finalized
2024-09-03 fixed logic stage diff amp updates + sim
2024-09-04 vertical logic stage complete
2024-09-05 minor
2024-09-06 pre meeting files
2024-09-06 removed extra parts
2024-09-08 almost completed new logic layout
2024-09-09 main portion of logic drc done
2024-09-10 final changes and bom with digikey and mouser PN
2024-09-11 brendans version of gerber files
2024-09-11 final tweaks to logic, silkscreen not done
2024-09-11 silkscreen on logic updated
2024-09-11 mounting hole update
2024-09-11 updated logic diffamps with avail. resistors
2024-09-11 qol silkscreen updates to logic
2024-09-11 more minor silkscreen tweaking logic
2024-09-15 schematic updates - logic
2024-09-17 created platformio project
2024-09-17 more changes
2024-09-17 stash
2024-09-18 updated resistor mappings for logic amps
2024-09-18 final dcv amp resistor vals
2024-09-22 startded
2024-09-23 infra for switching states
2024-09-23 add ADC configuration
2024-09-24 moved functions
2024-09-28 fix systick, hall implementation
2024-09-28 add parameter
2024-09-28 add abstraction for platform types
2024-09-28 beginnings of generic ADC interface
2024-09-29 started ADC driver
2024-09-29 templated all interfaces
2024-09-29 minor edits
2024-10-02 cleanup + timer interface/impl
2024-10-02 cleanup
2024-10-02 htim1 implementation (untested)
2024-10-03 add timer 2, remove peripheral external linkage
2024-10-04 add HEI environment
2024-10-08 added impl headers for HEI
2024-10-08 add HEI timer implementation
2024-10-09 add SVM calculation
2024-10-09 began implementing bridge state sequencing calc
2024-10-09 add bridge state sequence calculation
2024-10-09 bootstrap SVM
2024-10-09 svm set timer period
2024-10-09 fix state transitions
2024-10-20 notes on position estimation
2024-10-22 adc implementation
2024-10-23 hall implementation sans speed est.
2024-10-23 added horizontal b2b connector info/3d model
2024-10-23 added molex datasheet
2024-10-30 working SVM?
2024-10-30 cleanup & remove nucleo code
2024-10-31 fix dot product scaling
2024-10-31 fix sector 5 bug
2024-10-31 parameter cleanup
2024-11-09 smooth commutation, ADCs implemented
2024-11-09 added uart
2024-11-09 swapped ADC channel enum order to match results buffer; added .cfg file modification to repo for easy access
2024-11-22 many features
    added hall sense, rotor position offset learning routine, throttle control
    moved common variable definitions out of header file.
2024-11-28 speed observer

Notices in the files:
parts and their libraries:
Copyright 2021 Accelerated Designs. All rights reserved.
